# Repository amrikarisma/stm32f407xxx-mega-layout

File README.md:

# stm32f407xxx-mega-layout

## Made For Speeduino and RusEFI Firmware
This board is inspired by Pazi88 and Mega100 boards. Thank you very much to those who created the board first.

### Front

### Back

### Schematic 
[schematic-stm32f407xxx-mega-layout.pdf](schematic-stm32f407xxx-mega-layout.pdf)

### Thanks to
- https://github.com/pazi88/STM32_mega
- https://github.com/rusefi/fw-custom-mega100/

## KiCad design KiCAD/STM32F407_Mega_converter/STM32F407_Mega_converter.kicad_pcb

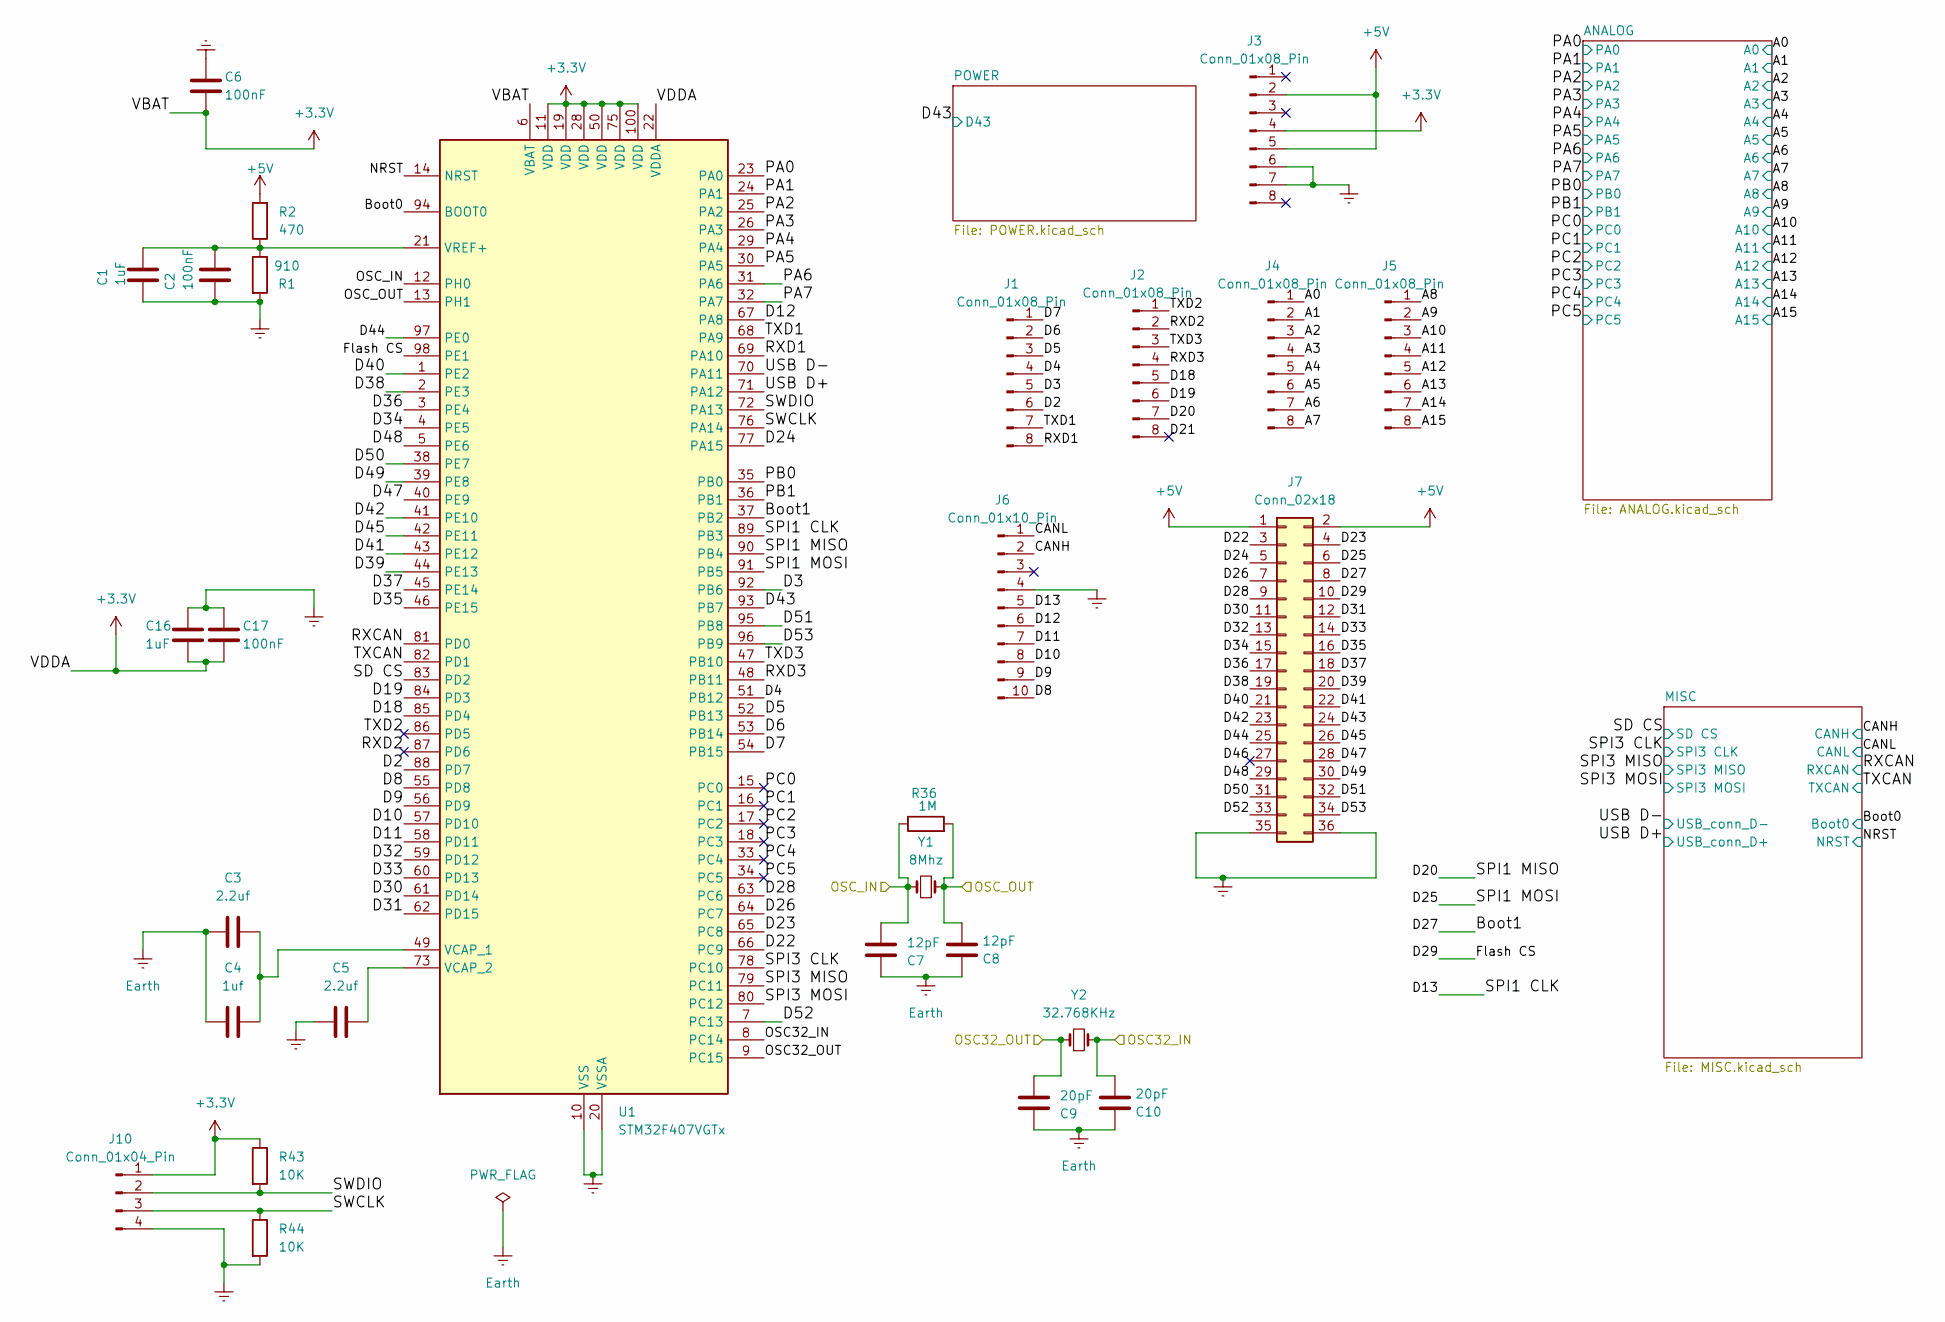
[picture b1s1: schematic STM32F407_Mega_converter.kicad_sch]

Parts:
C1, C16: 1uF; C_0603_1608Metric
C2, C6, C17: 100nF; C_0603_1608Metric
C3, C5: 2.2uf; C_0603_1608Metric
C4: 1uf; C_0603_1608Metric
C7, C8: 12pF; C_0603_1608Metric
C9, C10: 20pF; C_0603_1608Metric
J1, J2, J3, J4, J5: Conn_01x08_Pin; PinHeader_1x08_P2.54mm_Vertical
J6: Conn_01x10_Pin; PinHeader_1x10_P2.54mm_Vertical
J7: Conn_02x18; PinHeader_2x18_P2.54mm_Vertical
J10: Conn_01x04_Pin; PinHeader_1x04_P2.54mm_Vertical
R1: 910; R_0603_1608Metric
R2: 470; R_0603_1608Metric
R36: 1M; R_0603_1608Metric
R43, R44: 10K; R_0603_1608Metric
U1: STM32F407VGTx; LQFP-100_14x14mm_P0.5mm
Y1: 8Mhz; Crystal_SMD_5032-2Pin_5.0x3.2mm
Y2: 32.768KHz; Crystal_SMD_3215-2Pin_3.2x1.5mm

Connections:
+3.3V: C6.2, C16.1, C17.2, J3.4, J10.1, R43.1, U1.6 (VBAT), U1.11 (VDD), U1.19 (VDD), U1.22 (VDDA), U1.28 (VDD), U1.50 (VDD), U1.75 (VDD), U1.100 (VDD); also elsewhere on the board
+5V: J3.2, J3.5, J7.1, J7.2, R2.2; also elsewhere on the board
/A0: J4.1; also elsewhere on the board
/A1: J4.2; also elsewhere on the board
/A2: J4.3; also elsewhere on the board
/A3: J4.4; also elsewhere on the board
/A4: J4.5; also elsewhere on the board
/A5: J4.6; also elsewhere on the board
/A6: J4.7; also elsewhere on the board
/A7: J4.8; also elsewhere on the board
/A8: J5.1; also elsewhere on the board
/A9: J5.2; also elsewhere on the board
/A10: J5.3; also elsewhere on the board
/A11: J5.4; also elsewhere on the board
/A12: J5.5; also elsewhere on the board
/A13: J5.6; also elsewhere on the board
/A14: J5.7; also elsewhere on the board
/A15: J5.8; also elsewhere on the board
/Boot0: U1.94 (BOOT0); also elsewhere on the board
/Boot1: J7.8, U1.37 (PB2)
/CANH: J6.2; also elsewhere on the board
/CANL: J6.1; also elsewhere on the board
/D2: J1.6, U1.88 (PD7)
/D3: J1.5, U1.92 (PB6)
/D4: J1.4, U1.51 (PB12)
/D5: J1.3, U1.52 (PB13)
/D6: J1.2, U1.53 (PB14)
/D7: J1.1, U1.54 (PB15)
/D8: J6.10, U1.55 (PD8)
/D9: J6.9, U1.56 (PD9)
/D10: J6.8, U1.57 (PD10)
/D11: J6.7, U1.58 (PD11)
/D12: J6.6, U1.67 (PA8)
/D13: J6.5, U1.89 (PB3)
/D18: J2.5, U1.85 (PD4)
/D19: J2.6, U1.84 (PD3)
/D20: J2.7, U1.90 (PB4)
/D21: J2.8
/D22: J7.3, U1.66 (PC9)
/D23: J7.4, U1.65 (PC8)
/D24: J7.5, U1.77 (PA15)
/D25: J7.6, U1.91 (PB5)
/D26: J7.7, U1.64 (PC7)
/D28: J7.9, U1.63 (PC6)
/D29: J7.10, U1.98 (PE1)
/D30: J7.11, U1.61 (PD14)
/D31: J7.12, U1.62 (PD15)
/D32: J7.13, U1.59 (PD12)
/D33: J7.14, U1.60 (PD13)
/D34: J7.15, U1.4 (PE5)
/D35: J7.16, U1.46 (PE15)
/D36: J7.17, U1.3 (PE4)
/D37: J7.18, U1.45 (PE14)
/D38: J7.19, U1.2 (PE3)
/D39: J7.20, U1.44 (PE13)
/D40: J7.21, U1.1 (PE2)
/D41: J7.22, U1.43 (PE12)
/D42: J7.23, U1.41 (PE10)
/D43: J7.24, U1.93 (PB7); also elsewhere on the board
/D44: J7.25, U1.97 (PE0)
/D45: J7.26, U1.42 (PE11)
/D46: J7.27
/D47: J7.28, U1.40 (PE9)
/D48: J7.29, U1.5 (PE6)
/D49: J7.30, U1.39 (PE8)
/D50: J7.31, U1.38 (PE7)
/D51: J7.32, U1.95 (PB8)
/D52: J7.33, U1.7 (PC13)
/D53: J7.34, U1.96 (PB9)
/NRST: U1.14 (NRST); also elsewhere on the board
/OSC32_IN: C10.1, U1.8 (PC14), Y2.2
/OSC32_OUT: C9.1, U1.9 (PC15), Y2.1
/OSC_IN: C7.1, R36.1, U1.12 (PH0), Y1.1
/OSC_OUT: C8.1, R36.2, U1.13 (PH1), Y1.2
/PA0: U1.23 (PA0); also elsewhere on the board
/PA1: U1.24 (PA1); also elsewhere on the board
/PA2: U1.25 (PA2); also elsewhere on the board
/PA3: U1.26 (PA3); also elsewhere on the board
/PA4: U1.29 (PA4); also elsewhere on the board
/PA5: U1.30 (PA5); also elsewhere on the board
/PA6: U1.31 (PA6); also elsewhere on the board
/PA7: U1.32 (PA7); also elsewhere on the board
/PB0: U1.35 (PB0); also elsewhere on the board
/PB1: U1.36 (PB1); also elsewhere on the board
/PC0: U1.15 (PC0); also elsewhere on the board
/PC1: U1.16 (PC1); also elsewhere on the board
/PC2: U1.17 (PC2); also elsewhere on the board
/PC3: U1.18 (PC3); also elsewhere on the board
/PC4: U1.33 (PC4); also elsewhere on the board
/PC5: U1.34 (PC5); also elsewhere on the board
/RXCAN: U1.81 (PD0); also elsewhere on the board
/RXD1: J1.8, U1.69 (PA10)
/RXD2: J2.2, U1.87 (PD6)
/RXD3: J2.4, U1.48 (PB11)
/SD CS: U1.83 (PD2); also elsewhere on the board
/SPI3 CLK: U1.78 (PC10); also elsewhere on the board
/SPI3 MISO: U1.79 (PC11); also elsewhere on the board
/SPI3 MOSI: U1.80 (PC12); also elsewhere on the board
/SWCLK: J10.3, R44.1, U1.76 (PA14)
/SWDIO: J10.2, R43.2, U1.72 (PA13)
/TXCAN: U1.82 (PD1); also elsewhere on the board
/TXD1: J1.7, U1.68 (PA9)
/TXD2: J2.1, U1.86 (PD5)
/TXD3: J2.3, U1.47 (PB10)
/USB D+: U1.71 (PA12); also elsewhere on the board
/USB D-: U1.70 (PA11); also elsewhere on the board
Earth: C1.1, C2.2, C3.1, C4.1, C5.1, C6.1, C7.2, C8.2, C9.2, C10.2, C16.2, C17.1, J3.6, J3.7, J6.4, J7.35, J7.36, J10.4, R1.2, R44.2, U1.10 (VSS), U1.20 (VSSA), U1.27 (VSS), U1.74 (VSS), U1.99 (VSS); also elsewhere on the board
unnamed: C3.2, C4.2, U1.49 (VCAP_1)
unnamed: C5.2, U1.73 (VCAP_2)
unnamed: C1.2, C2.1, R1.1, R2.1, U1.21 (VREF+)

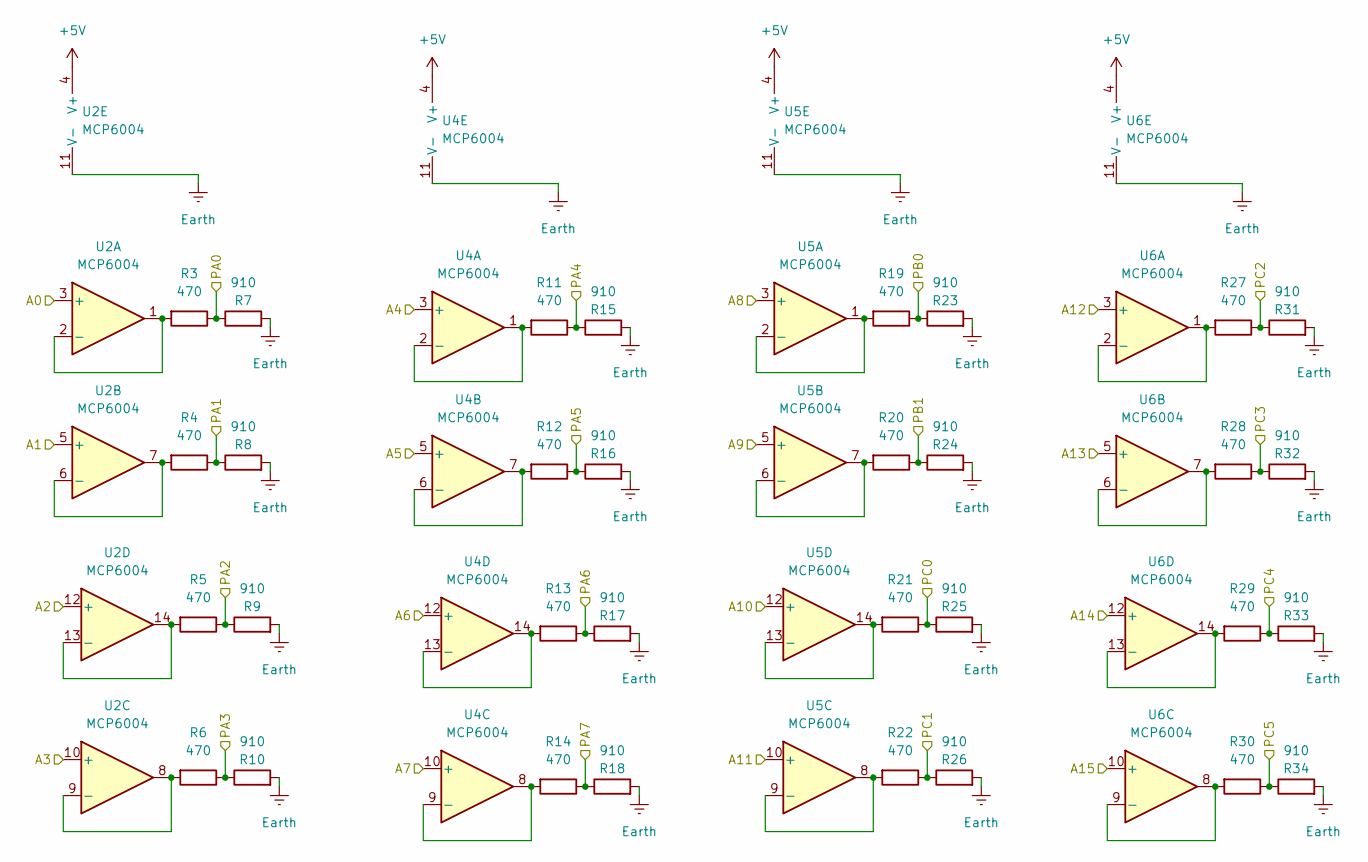
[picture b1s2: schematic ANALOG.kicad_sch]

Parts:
R3, R4, R5, R6, R11, R12, R13, R14, R19, R20, R21, R22, R27, R28, R29, R30: 470; R_0603_1608Metric
R7, R8, R9, R10, R15, R16, R17, R18, R23, R24, R25, R26, R31, R32, R33, R34: 910; R_0603_1608Metric
U2, U4, U5, U6: MCP6004; SOIC127P600X175-14N

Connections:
+5V: U2.4 (V+), U4.4 (V+), U5.4 (V+), U6.4 (V+); also elsewhere on the board
/A0: U2.3 (+); also elsewhere on the board
/A1: U2.5 (+); also elsewhere on the board
/A2: U2.12 (+); also elsewhere on the board
/A3: U2.10 (+); also elsewhere on the board
/A4: U4.3 (+); also elsewhere on the board
/A5: U4.5 (+); also elsewhere on the board
/A6: U4.12 (+); also elsewhere on the board
/A7: U4.10 (+); also elsewhere on the board
/A8: U5.3 (+); also elsewhere on the board
/A9: U5.5 (+); also elsewhere on the board
/A10: U5.12 (+); also elsewhere on the board
/A11: U5.10 (+); also elsewhere on the board
/A12: U6.3 (+); also elsewhere on the board
/A13: U6.5 (+); also elsewhere on the board
/A14: U6.12 (+); also elsewhere on the board
/A15: U6.10 (+); also elsewhere on the board
/PA0: R3.1, R7.1; also elsewhere on the board
/PA1: R4.1, R8.1; also elsewhere on the board
/PA2: R5.1, R9.1; also elsewhere on the board
/PA3: R6.1, R10.1; also elsewhere on the board
/PA4: R11.1, R15.1; also elsewhere on the board
/PA5: R12.1, R16.1; also elsewhere on the board
/PA6: R13.1, R17.1; also elsewhere on the board
/PA7: R14.1, R18.1; also elsewhere on the board
/PB0: R19.1, R23.1; also elsewhere on the board
/PB1: R20.1, R24.1; also elsewhere on the board
/PC0: R21.1, R25.1; also elsewhere on the board
/PC1: R22.1, R26.1; also elsewhere on the board
/PC2: R27.1, R31.1; also elsewhere on the board
/PC3: R28.1, R32.1; also elsewhere on the board
/PC4: R29.1, R33.1; also elsewhere on the board
/PC5: R30.1, R34.1; also elsewhere on the board
Earth: R7.2, R8.2, R9.2, R10.2, R15.2, R16.2, R17.2, R18.2, R23.2, R24.2, R25.2, R26.2, R31.2, R32.2, R33.2, R34.2, U2.11 (V-), U4.11 (V-), U5.11 (V-), U6.11 (V-); also elsewhere on the board
unnamed: R3.2, U2.1, U2.2 (-)
unnamed: R4.2, U2.6 (-), U2.7
unnamed: R6.2, U2.8, U2.9 (-)
unnamed: R5.2, U2.13 (-), U2.14
unnamed: R11.2, U4.1, U4.2 (-)
unnamed: R12.2, U4.6 (-), U4.7
unnamed: R14.2, U4.8, U4.9 (-)
unnamed: R13.2, U4.13 (-), U4.14
unnamed: R19.2, U5.1, U5.2 (-)
unnamed: R20.2, U5.6 (-), U5.7
unnamed: R22.2, U5.8, U5.9 (-)
unnamed: R21.2, U5.13 (-), U5.14
unnamed: R27.2, U6.1, U6.2 (-)
unnamed: R28.2, U6.6 (-), U6.7
unnamed: R30.2, U6.8, U6.9 (-)
unnamed: R29.2, U6.13 (-), U6.14

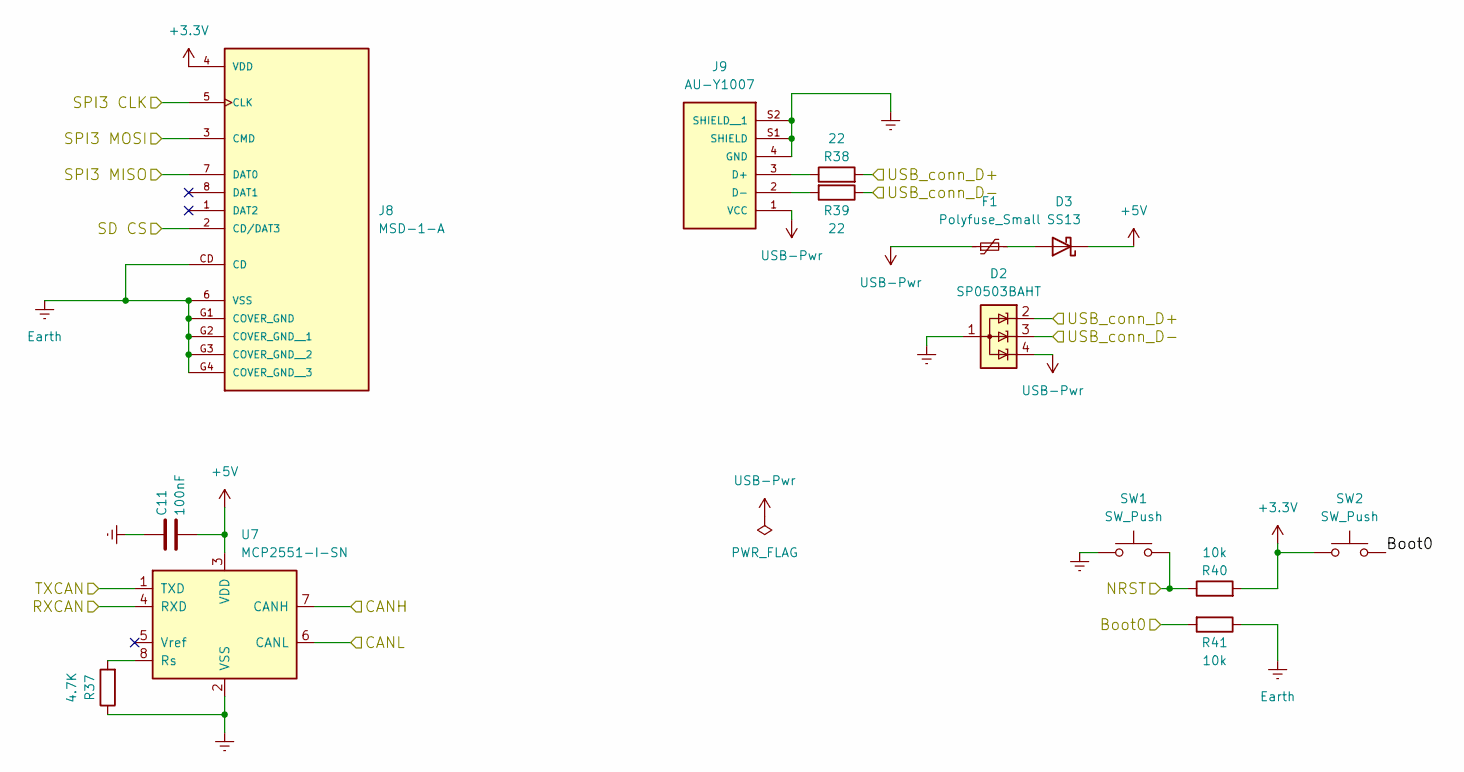
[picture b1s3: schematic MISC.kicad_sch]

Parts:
C11: 100nF; C_0603_1608Metric
D2: SP0503BAHT; SOT-143
D3: SS13; D_SMA
F1: Polyfuse_Small; Fuse_1206_3216Metric
J8: MSD-1-A; CUI_MSD-1-A; PARTREV 1.0
J9: AU-Y1007; ASSMANN_USB_TYPE-B; PARTREV 01
R37: 4.7K; R_0603_1608Metric
R38, R39: 22; R_0603_1608Metric
R40, R41: 10k; R_0603_1608Metric
SW1, SW2: SW_Push; SW_SPST_CK_RS282G05A3
U7: MCP2551-I-SN; SOIC-8_3.9x4.9mm_P1.27mm

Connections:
+3.3V: J8.4 (VDD), R40.2, SW2.1; also elsewhere on the board
+5V: C11.2, D3.1 (K), U7.3 (VDD); also elsewhere on the board
/Boot0: R41.2, SW2.2; also elsewhere on the board
/CANH: U7.7 (CANH); also elsewhere on the board
/CANL: U7.6 (CANL); also elsewhere on the board
/NRST: R40.1, SW1.2; also elsewhere on the board
/RXCAN: U7.4 (RXD); also elsewhere on the board
/SD CS: J8.2 (CD/DAT3); also elsewhere on the board
/SPI3 CLK: J8.5 (CLK); also elsewhere on the board
/SPI3 MISO: J8.7 (DAT0); also elsewhere on the board
/SPI3 MOSI: J8.3 (CMD); also elsewhere on the board
/TXCAN: U7.1 (TXD); also elsewhere on the board
/USB D+: D2.2 (K), R38.2; also elsewhere on the board
/USB D-: D2.3 (K), R39.1; also elsewhere on the board
Earth: C11.1, D2.1 (A), J8.6 (VSS), J8.CD, J8.G1 (COVER_GND), J8.G2 (COVER_GND__1), J8.G3 (COVER_GND__2), J8.G4 (COVER_GND__3), J9.4 (GND), J9.S1 (SHIELD), J9.S2 (SHIELD__1), R37.1, R41.1, SW1.1, U7.2 (VSS); also elsewhere on the board
unnamed: D3.2 (A), F1.2
unnamed: J9.3 (D+), R38.1
unnamed: J9.2 (D-), R39.2
unnamed: R37.2, U7.8 (Rs)
USB-Pwr: D2.4 (K), F1.1, J9.1 (VCC)

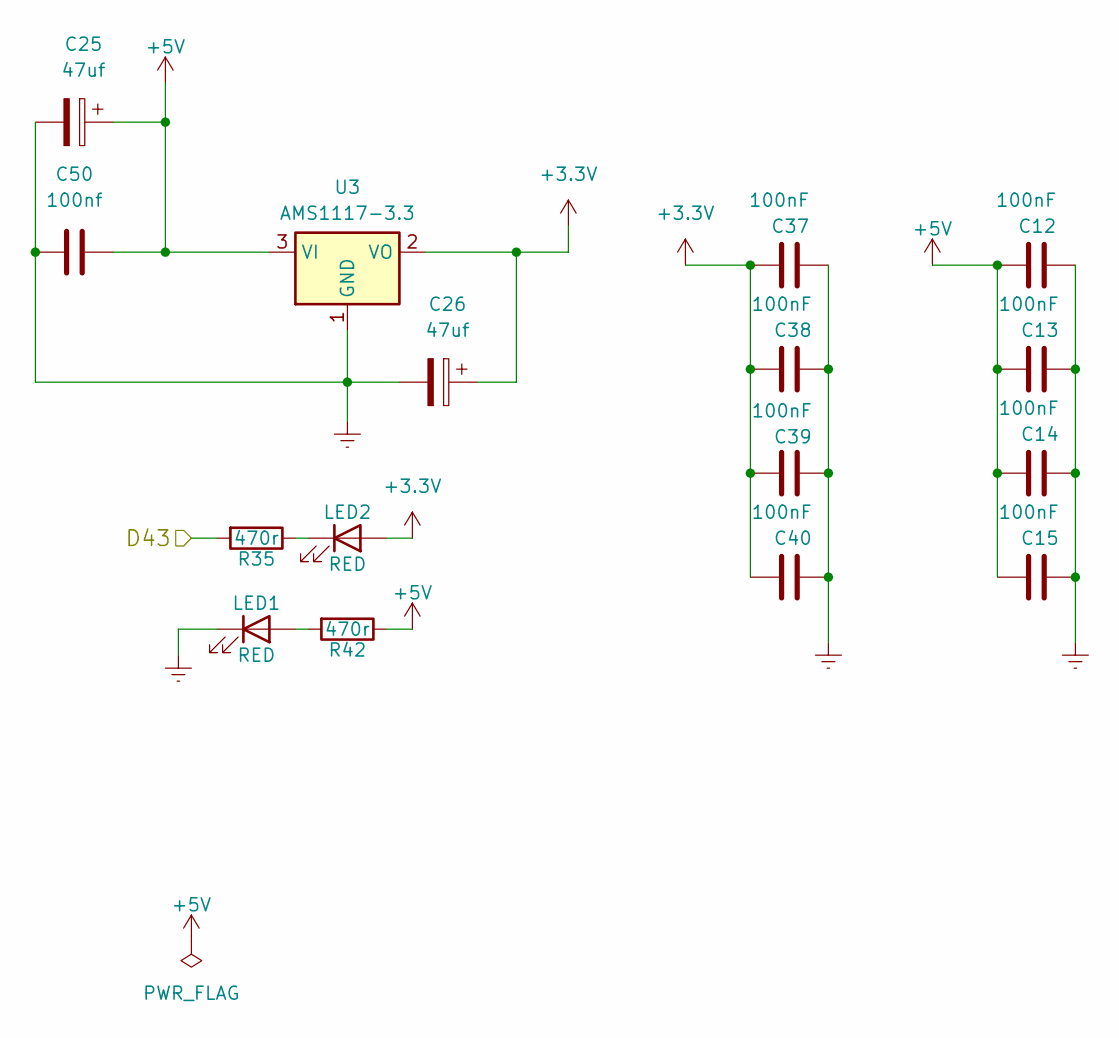
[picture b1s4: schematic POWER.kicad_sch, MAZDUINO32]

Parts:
C12, C13, C14, C15, C37, C38, C39, C40: 100nF; C_0603_1608Metric
C25, C26: 47uf; CP_Elec_5x5.4
C50: 100nf; C_0603_1608Metric
LED1, LED2: RED; LED_0805_2012Metric; MPN SML-310LTT86
R35, R42: 470r; R_0805_2012Metric; MPN RK73H2ATTD4700F
U3: AMS1117-3.3; SOT-223-3_TabPin2

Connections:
+3.3V: C26.1, C37.1, C38.1, C39.1, C40.1, LED2.2 (A), U3.2 (VO); also elsewhere on the board
+5V: C12.1, C13.1, C14.1, C15.1, C25.1, C50.2, R42.1, U3.3 (VI); also elsewhere on the board
/D43: R35.2; also elsewhere on the board
Earth: C12.2, C13.2, C14.2, C15.2, C25.2, C26.2, C37.2, C38.2, C39.2, C40.2, C50.1, LED1.1 (K), U3.1 (GND); also elsewhere on the board
unnamed: LED1.2 (A), R42.2
unnamed: LED2.1 (K), R35.1

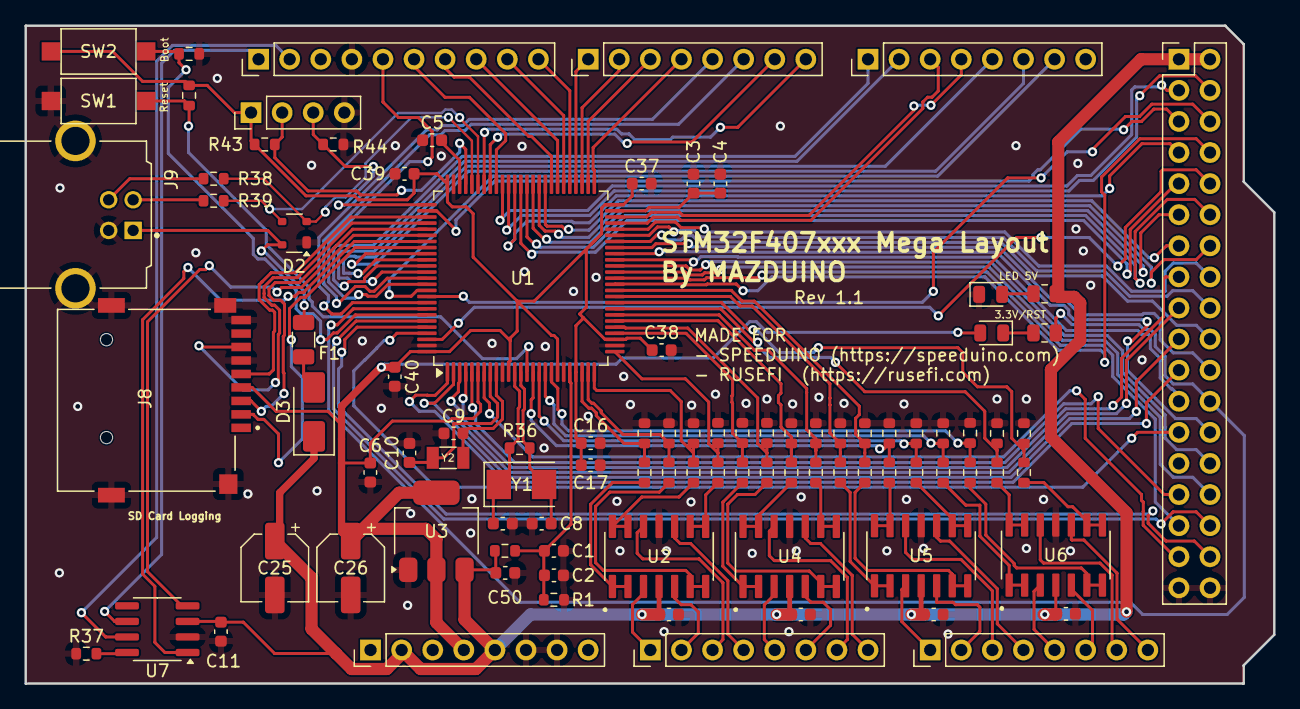
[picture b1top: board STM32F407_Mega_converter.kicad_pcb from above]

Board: 2 copper layers, 102.0 x 53.8 mm, 94 parts (0 on the bottom side), 131 nets.

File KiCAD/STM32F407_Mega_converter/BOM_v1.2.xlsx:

Qty | Reference | Value | Footprint
2 | C1,C16 | 1uF | Capacitor_SMD:C_0603_1608Metric
12 | C2,C6,C11,C12,C13,C14,C15,C17,C37,C38,C39,C40 | 100nF | Capacitor_SMD:C_0603_1608Metric
2 | C3,C5 | 2.2uf | Capacitor_SMD:C_0603_1608Metric
1 | C4 | 1uf | Capacitor_SMD:C_0603_1608Metric
2 | C7,C8 | 12pF | Capacitor_SMD:C_0603_1608Metric
2 | C9,C10 | 20pF | Capacitor_SMD:C_0603_1608Metric
2 | C25,C26 | 47uf | Capacitor_SMD:CP_Elec_5x5.4
1 | C50 | 100nf | Capacitor_SMD:C_0603_1608Metric
1 | D2 | SP0503BAHT | Package_TO_SOT_SMD:SOT-143
1 | D3 | SS13 | Diode_SMD:D_SMA
1 | F1 | Polyfuse_Small | Fuse:Fuse_1206_3216Metric
5 | J1,J2,J3,J4,J5 | Conn_01x08_Pin | Connector_PinHeader_2.54mm:PinHeader_1x08_P2.54mm_Vertical
1 | J6 | Conn_01x10_Pin | Connector_PinHeader_2.54mm:PinHeader_1x10_P2.54mm_Vertical
1 | J7 | Conn_02x18 | Connector_PinHeader_2.54mm:PinHeader_2x18_P2.54mm_Vertical
1 | J8 | MSD-1-A | MSD_1_A:CUI_MSD-1-A
1 | J9 | AU-Y1007 | USB_TYPE-B:ASSMANN_USB_TYPE-B
1 | J10 | Conn_01x04_Pin | Connector_PinHeader_2.54mm:PinHeader_1x04_P2.54mm_Vertical
2 | LED1,LED2 | RED | LED_SMD:LED_0805_2012Metric
17 | R1,R7,R8,R9,R10,R15,R16,R17,R18,R23,R24,R25,R26,R31,R32,R33,R34 | 910 | Resistor_SMD:R_0603_1608Metric
17 | R2,R3,R4,R5,R6,R11,R12,R13,R14,R19,R20,R21,R22,R27,R28,R29,R30 | 470 | Resistor_SMD:R_0603_1608Metric
2 | R35,R42 | 470r | Resistor_SMD:R_0805_2012Metric
1 | R36 | 1M | Resistor_SMD:R_0603_1608Metric
1 | R37 | 4.7K | Resistor_SMD:R_0603_1608Metric
2 | R38,R39 | 22 | Resistor_SMD:R_0603_1608Metric
2 | R40,R41 | 10k | Resistor_SMD:R_0603_1608Metric
2 | R43,R44 | 10K | Resistor_SMD:R_0603_1608Metric
2 | SW1,SW2 | SW_Push | Button_Switch_SMD:SW_SPST_CK_RS282G05A3
1 | U1 | STM32F407VGTx | Package_QFP:LQFP-100_14x14mm_P0.5mm
4 | U2,U4,U5,U6 | MCP6004 | MCP6004T_I_SL:SOIC127P600X175-14N
1 | U3 | AMS1117-3.3 | Package_TO_SOT_SMD:SOT-223-3_TabPin2
1 | U7 | MCP2551-I-SN | Package_SO:SOIC-8_3.9x4.9mm_P1.27mm
1 | Y1 | 8Mhz | Crystal:Crystal_SMD_5032-2Pin_5.0x3.2mm
1 | Y2 | 32.768KHz | Crystal:Crystal_SMD_3215-2Pin_3.2x1.5mm

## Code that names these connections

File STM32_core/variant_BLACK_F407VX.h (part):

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/*----------------------------------------------------------------------------
 *        STM32 pins number
 *----------------------------------------------------------------------------*/
#define PC9                      0 // D22
#define PC8                      1 // D23
#define PD7                      2 // D2
#define PB6                      3 // D3
#define PB12                     4 // D4
#define PB13                     5 // D5
#define PB14                      6 // D6
#define PB15                      7 // D7
#define PD8                     8 // D8
#define PD9                     9 // D9
#define PD10                     10 // D10
#define PD11                     11 // D11
#define PA8                      12 // D12
#define PB3                      13 // D13
#define PB10                      14 // D16
#define PB11                      15 // D17
#define PC12                     16 // SPI3 MOSI for SD
#define PC11                     17 // SPI3 MISO for SD
#define PD4                      18 // D18
#define PD3                      19 // D19
#define PD0                      20 // CAN RX
#define PD1                      21 // CAN TX
#define PA10                     22 // D0
#define PA9                      23 // D1
#define PA15                     24 // D24
#define PD5                     25 // D14
#define PC7                      26 // D26
#define PD6                     27 // D15
#define PC6                      28 // D28
#define PC10                     29 // SPI3 CLK for SD
#define PD14                     30 // D30
#define PD15                     31 // D31
#define PD12                     32 // D32
#define PD13                     33 // D33
#define PE5                      34 // D34
#define PE15                     35 // D35
#define PE4                      36 // D36
#define PE14                     37 // D37
#define PE3                      38 // D38
#define PE13                     39 // D39
#define PE2                      40 // D40
#define PE12                     41 // D41
#define PE10                     42 // D42
#define PB7                      43 // D43
#define PE0                      44 // SPI1 CLK
#define PE11                     45 // D45
#define PD2                      46 // D46 // SD CS
#define PE9                      47 // D47
#define PE6                      48 // D48
#define PE8                      49 // D49
#define PE7                      50 // D50
#define PB8                      51 // D51
#define PC13                     52 // D52
#define PB9                      53 // D53
#define PA0                      PIN_A0
#define PA1                      PIN_A1
#define PA2                      PIN_A2
#define PA3                      PIN_A3
#define PA4                      PIN_A4
#define PA5                      PIN_A5
#define PA6                      PIN_A6
#define PA7                      PIN_A7
#define PB0                      PIN_A8
#define PB1                      PIN_A9
#define PC0                      PIN_A10
#define PC1                      PIN_A11
#define PC2                      PIN_A12
#define PC3                      PIN_A13
#define PC4                      PIN_A14
#define PC5                      PIN_A15
#define PA11                     70 // USB_DP
#define PA12                     71 // USB_DM
#define PE1                      72 // SPI-Flash CS
#define PB4                      73 // SPI1 MOSI
#define PB5                      74 // SPI1 MISO

// Alternate pins number
#define PA0_ALT1                (PA0  | ALT1)
#define PA0_ALT2                (PA0  | ALT2)
#define PA1_ALT1                (PA1  | ALT1)
#define PA1_ALT2                (PA1  | ALT2)
#define PA2_ALT1                (PA2  | ALT1)
#define PA2_ALT2                (PA2  | ALT2)
#define PA3_ALT1                (PA3  | ALT1)
#define PA3_ALT2                (PA3  | ALT2)
#define PA4_ALT1                (PA4  | ALT1)
#define PA5_ALT1                (PA5  | ALT1)
#define PA6_ALT1                (PA6  | ALT1)
#define PA7_ALT1                (PA7  | ALT1)
#define PA7_ALT2                (PA7  | ALT2)
#define PA7_ALT3                (PA7  | ALT3)
#define PA15_ALT1               (PA15 | ALT1)
#define PB0_ALT1                (PB0  | ALT1)
#define PB0_ALT2                (PB0  | ALT2)
#define PB1_ALT1                (PB1  | ALT1)
#define PB1_ALT2                (PB1  | ALT2)
#define PB3_ALT1                (PB3  | ALT1)
#define PB4_ALT1                (PB4  | ALT1)
#define PB5_ALT1                (PB5  | ALT1)
#define PB8_ALT1                (PB8  | ALT1)
#define PB9_ALT1                (PB9  | ALT1)
#define PB14_ALT1               (PB14 | ALT1)
#define PB14_ALT2               (PB14 | ALT2)
#define PB15_ALT1               (PB15 | ALT1)
#define PB15_ALT2               (PB15 | ALT2)
#define PC0_ALT1                (PC0  | ALT1)
#define PC0_ALT2                (PC0  | ALT2)
#define PC1_ALT1                (PC1  | ALT1)
#define PC1_ALT2                (PC1  | ALT2)
#define PC2_ALT1                (PC2  | ALT1)
#define PC2_ALT2                (PC2  | ALT2)
#define PC3_ALT1                (PC3  | ALT1)
#define PC3_ALT2                (PC3  | ALT2)
#define PC4_ALT1                (PC4  | ALT1)
#define PC5_ALT1                (PC5  | ALT1)
#define PC6_ALT1                (PC6  | ALT1)
#define PC7_ALT1                (PC7  | ALT1)
#define PC8_ALT1                (PC8  | ALT1)
#define PC9_ALT1                (PC9  | ALT1)
#define PC10_ALT1               (PC10 | ALT1)
#define PC11_ALT1               (PC11 | ALT1)

#define NUM_DIGITAL_PINS        75
#define NUM_ANALOG_INPUTS       16
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// On-board LED pin number

#ifndef LED_BUILTIN
  #define LED_BUILTIN           PB7
#endif

// Below SPI and I2C definitions already done in the core
// Could be redefined here if differs from the default one
// SPI Definitions
#ifndef PIN_SPI_SS
  #define PIN_SPI_SS            PE1 // W25Q16 (on board flash)
#endif
#ifndef PIN_SPI_SS1
  #define PIN_SPI_SS1           PE1 // W25Q16 (on board flash)
#endif
#ifndef PIN_SPI_MOSI
  #define PIN_SPI_MOSI          PB5 // W25Q16 (on board flash)
#endif
#ifndef PIN_SPI_MISO
  #define PIN_SPI_MISO          PB4 // W25Q16 (on board flash)
#endif
#ifndef PIN_SPI_SCK
  #define PIN_SPI_SCK           PB3 // W25Q16 (on board flash)
#endif

// I2C Definitions
#ifndef PIN_WIRE_SDA
  #define PIN_WIRE_SDA          PB9
#endif
#ifndef PIN_WIRE_SCL
  #define PIN_WIRE_SCL          PB8
#endif

// Timer Definitions
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// Default pin used for 'Serial' instance
// Mandatory for Firmata
#ifndef PIN_SERIAL_RX
  #define PIN_SERIAL_RX         PA10
#endif
#ifndef PIN_SERIAL_TX
  #define PIN_SERIAL_TX         PA9
#endif

/* Extra HAL modules */
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
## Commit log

2025-02-20 add kicad
2025-02-22 update rev1.2 fix sdcard conflict with ua4c board connector
2025-08-01 add firmware speeduino
2025-08-05 update prebuild with sdcard logging
2025-08-09 update mapping arduino digital ppin
2025-08-09 fix mapping pin
2025-08-09 add rusefi firmware

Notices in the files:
STM32_core/variant_BLACK_F407VX.h:
Copyright (c) 2017-2021, STMicroelectronics
All rights reserved.
This software component is licensed by ST under BSD 3-Clause license,
the "License"; You may not use this file except in compliance with the
License. You may obtain a copy of the License at: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
